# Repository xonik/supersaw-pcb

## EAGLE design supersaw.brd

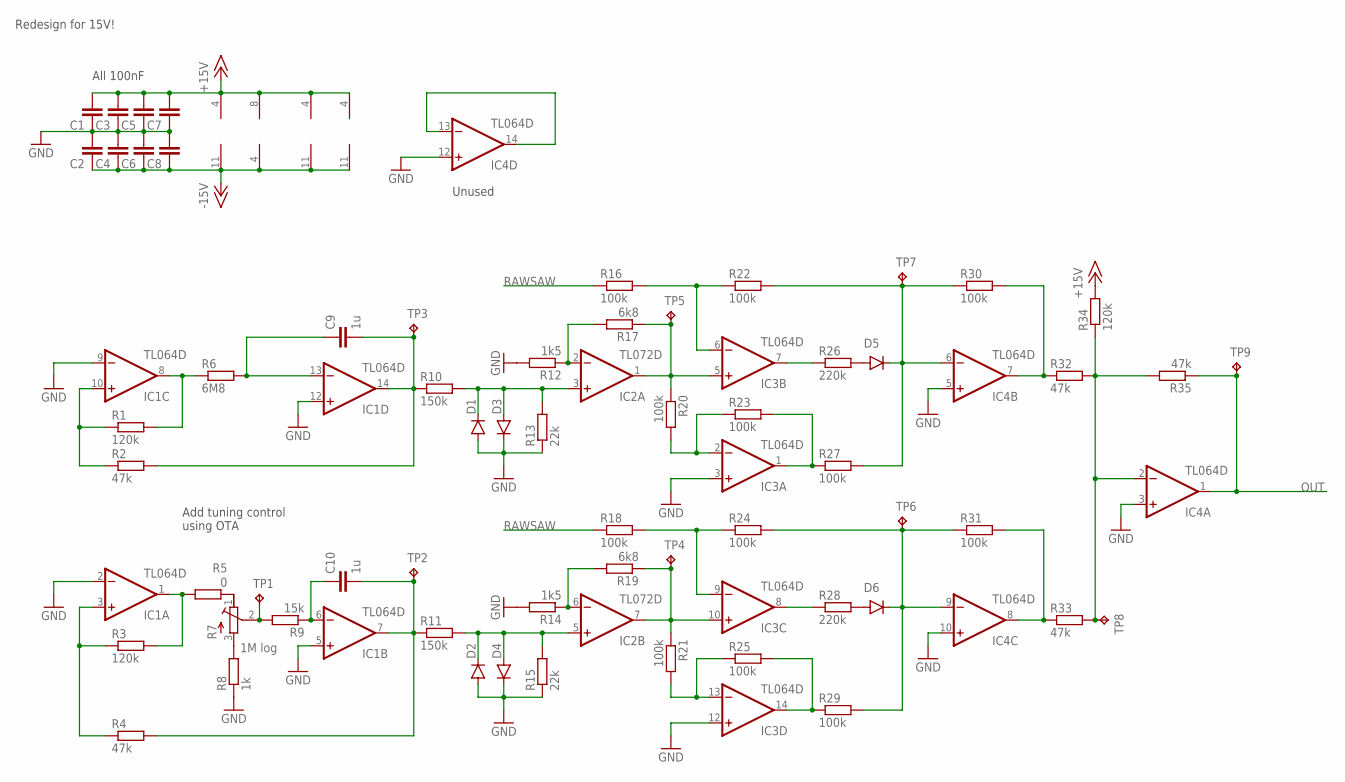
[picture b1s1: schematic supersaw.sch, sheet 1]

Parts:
C1, C2, C3, C4, C5, C6, C7, C8: 100n; C0805
C9, C10: 1u; C0805
D1, D2, D3, D4, D5, D6: 1N41480805; D0805-J
IC1, IC3, IC4: TL064D; SO14
IC2: TL072D; SO08J
R1, R3, R34: 120k; R0805
R2, R4, R32, R33, R35: 47k; R0805
R5: 0; R0805
R6: 6M8; R0805
R7: 1M log; RTRIMT93XA
R8: 1k; R0805
R9: 15k; R0805
R10, R11: 150k; R0805
R12, R14: 1k5; R0805
R13, R15: 22k; R0805
R16, R18, R20, R21, R22, R23, R24, R25, R27, R29, R30, R31: 100k; R0805
R17, R19: 6k8; R0805
R26, R28: 220k; R0805
TP1, TP2, TP3, TP4, TP5, TP6, TP7, TP8, TP9: TPB2,54; B2,54

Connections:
+15V: C1.2, C3.2, C5.2, C7.2, IC1.4 (V+), IC2.8 (V+), IC3.4 (V+), IC4.4 (V+), R34.2
-15V: C2.1, C4.1, C6.1, C8.1, IC1.11 (V-), IC2.4 (V-), IC3.11 (V-), IC4.11 (V-)
GND: C1.1, C2.2, C3.1, C4.2, C5.1, C6.2, C7.1, C8.2, D1.A, D2.A, D3.C, D4.C, IC1.2 (-IN), IC1.5 (+IN), IC1.9 (-IN), IC1.12 (+IN), IC3.3 (+IN), IC3.12 (+IN), IC4.3 (+IN), IC4.5 (+IN), IC4.10 (+IN), IC4.12 (+IN), R8.1, R12.2, R13.1, R14.2, R15.1
unnamed: IC4.13 (-IN), IC4.14 (OUT)
unnamed: IC1.10 (+IN), R1.1, R2.1
unnamed: IC1.3 (+IN), R3.1, R4.1
unnamed: IC1.8 (OUT), R1.2, R6.1
unnamed: C9.1, IC1.13 (-IN), R6.2
unnamed: D1.C, D3.A, IC2.3 (+IN), R10.2, R13.2
unnamed: IC1.1 (OUT), R3.2, R5.2
unnamed: C9.2, IC1.14 (OUT), R2.2, R10.1, TP3.TP
unnamed: R7.2 (S), R9.2, TP1.TP
unnamed: C10.1, IC1.6 (-IN), R9.1
unnamed: R7.3 (E), R8.2
unnamed: R5.1, R7.1 (A)
unnamed: C10.2, IC1.7 (OUT), R4.2, R11.1, TP2.TP
unnamed: D5.C, IC4.6 (-IN), R22.2, R27.2, R30.1, TP7.TP
unnamed: D2.C, D4.A, IC2.5 (+IN), R11.2, R15.2
unnamed: D6.C, IC4.9 (-IN), R24.2, R29.2, R31.1, TP6.TP
unnamed: IC2.2 (-IN), R12.1, R17.2
unnamed: IC2.6 (-IN), R14.1, R19.2
unnamed: IC2.1 (OUT), IC3.5 (+IN), R17.1, R20.1, TP5.TP
unnamed: IC2.7 (OUT), IC3.10 (+IN), R19.1, R21.1, TP4.TP
unnamed: IC3.6 (-IN), R16.2, R22.1
unnamed: IC3.7 (OUT), R26.1
unnamed: IC3.9 (-IN), R18.2, R24.1
unnamed: IC3.8 (OUT), R28.1
unnamed: D5.A, R26.2
unnamed: D6.A, R28.2
unnamed: IC3.1 (OUT), R23.2, R27.1
unnamed: IC3.14 (OUT), R25.2, R29.1
unnamed: IC3.2 (-IN), R20.2, R23.1
unnamed: IC4.2 (-IN), R32.2, R33.2, R34.1, R35.2, TP8.TP
unnamed: IC3.13 (-IN), R21.2, R25.1
unnamed: IC4.7 (OUT), R30.2, R32.1
unnamed: IC4.8 (OUT), R31.2, R33.1
OUT: IC4.1 (OUT), R35.1, TP9.TP
RAWSAW: R16.1, R18.1

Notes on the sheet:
Add tuning control using OTA
Redesign for 15V!
Unused
All 100nF

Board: 2 copper layers, 64 parts (0 on the bottom side), 38 nets, no tracks yet.

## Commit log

2018-08-02 Initial commit - full super saw circuit from minibrute
2020-02-26 Added git ignore
